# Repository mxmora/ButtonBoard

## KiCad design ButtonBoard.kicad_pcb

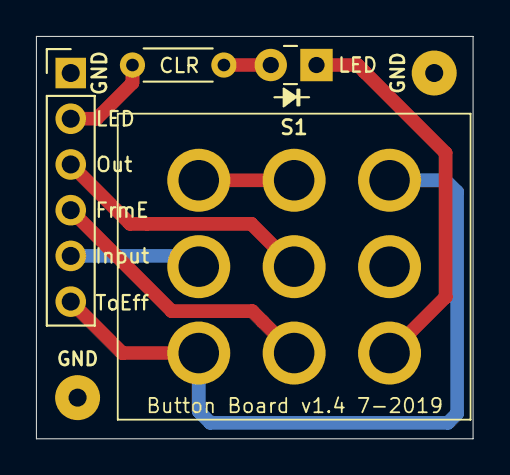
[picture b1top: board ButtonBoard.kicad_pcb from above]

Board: 2 copper layers, 24.3 x 22.4 mm, 6 parts (0 on the bottom side), 9 nets.

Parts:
CLR: 1k; R_Axial_DIN0204_L3.6mm_D1.6mm_P5.08mm_Horizontal
D1: LED; LED_Rectangular_W3.0mm_H2.0mm
GND: MountingHole_Pad; SolderWirePad_single_1mmDrill
GND#2: MountingHole_Pad; SolderWirePad_single_1mmDrill
J1: GND; PinHeader_1x06_P2.54mm_Vertical
S1: SF17020F-0302-21R-L-015; Footswitch_3PDT

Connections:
FromEffect: J1.4, S1.4
GND: GND.1, GND#2.1, J1.1, S1.2
Input: J1.5, S1.8
unnamed: D1.1, S1.1
unnamed: CLR.2, D1.2
unnamed: CLR.1, J1.2
unnamed: S1.6, S1.9
Output: J1.3, S1.5
ToEffect: J1.6, S1.3, S1.7

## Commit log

2019-05-17 rearrange and plot for build
2019-05-23 fix pin size bump version to 1.1
2019-05-23 Fix footswitch
2019-07-01 Bump to version 1.2 make the holes a little bigger
2019-07-02 re arrange some pins and ground the toEffect pin when bypassed
2019-07-11 update board with better connector
